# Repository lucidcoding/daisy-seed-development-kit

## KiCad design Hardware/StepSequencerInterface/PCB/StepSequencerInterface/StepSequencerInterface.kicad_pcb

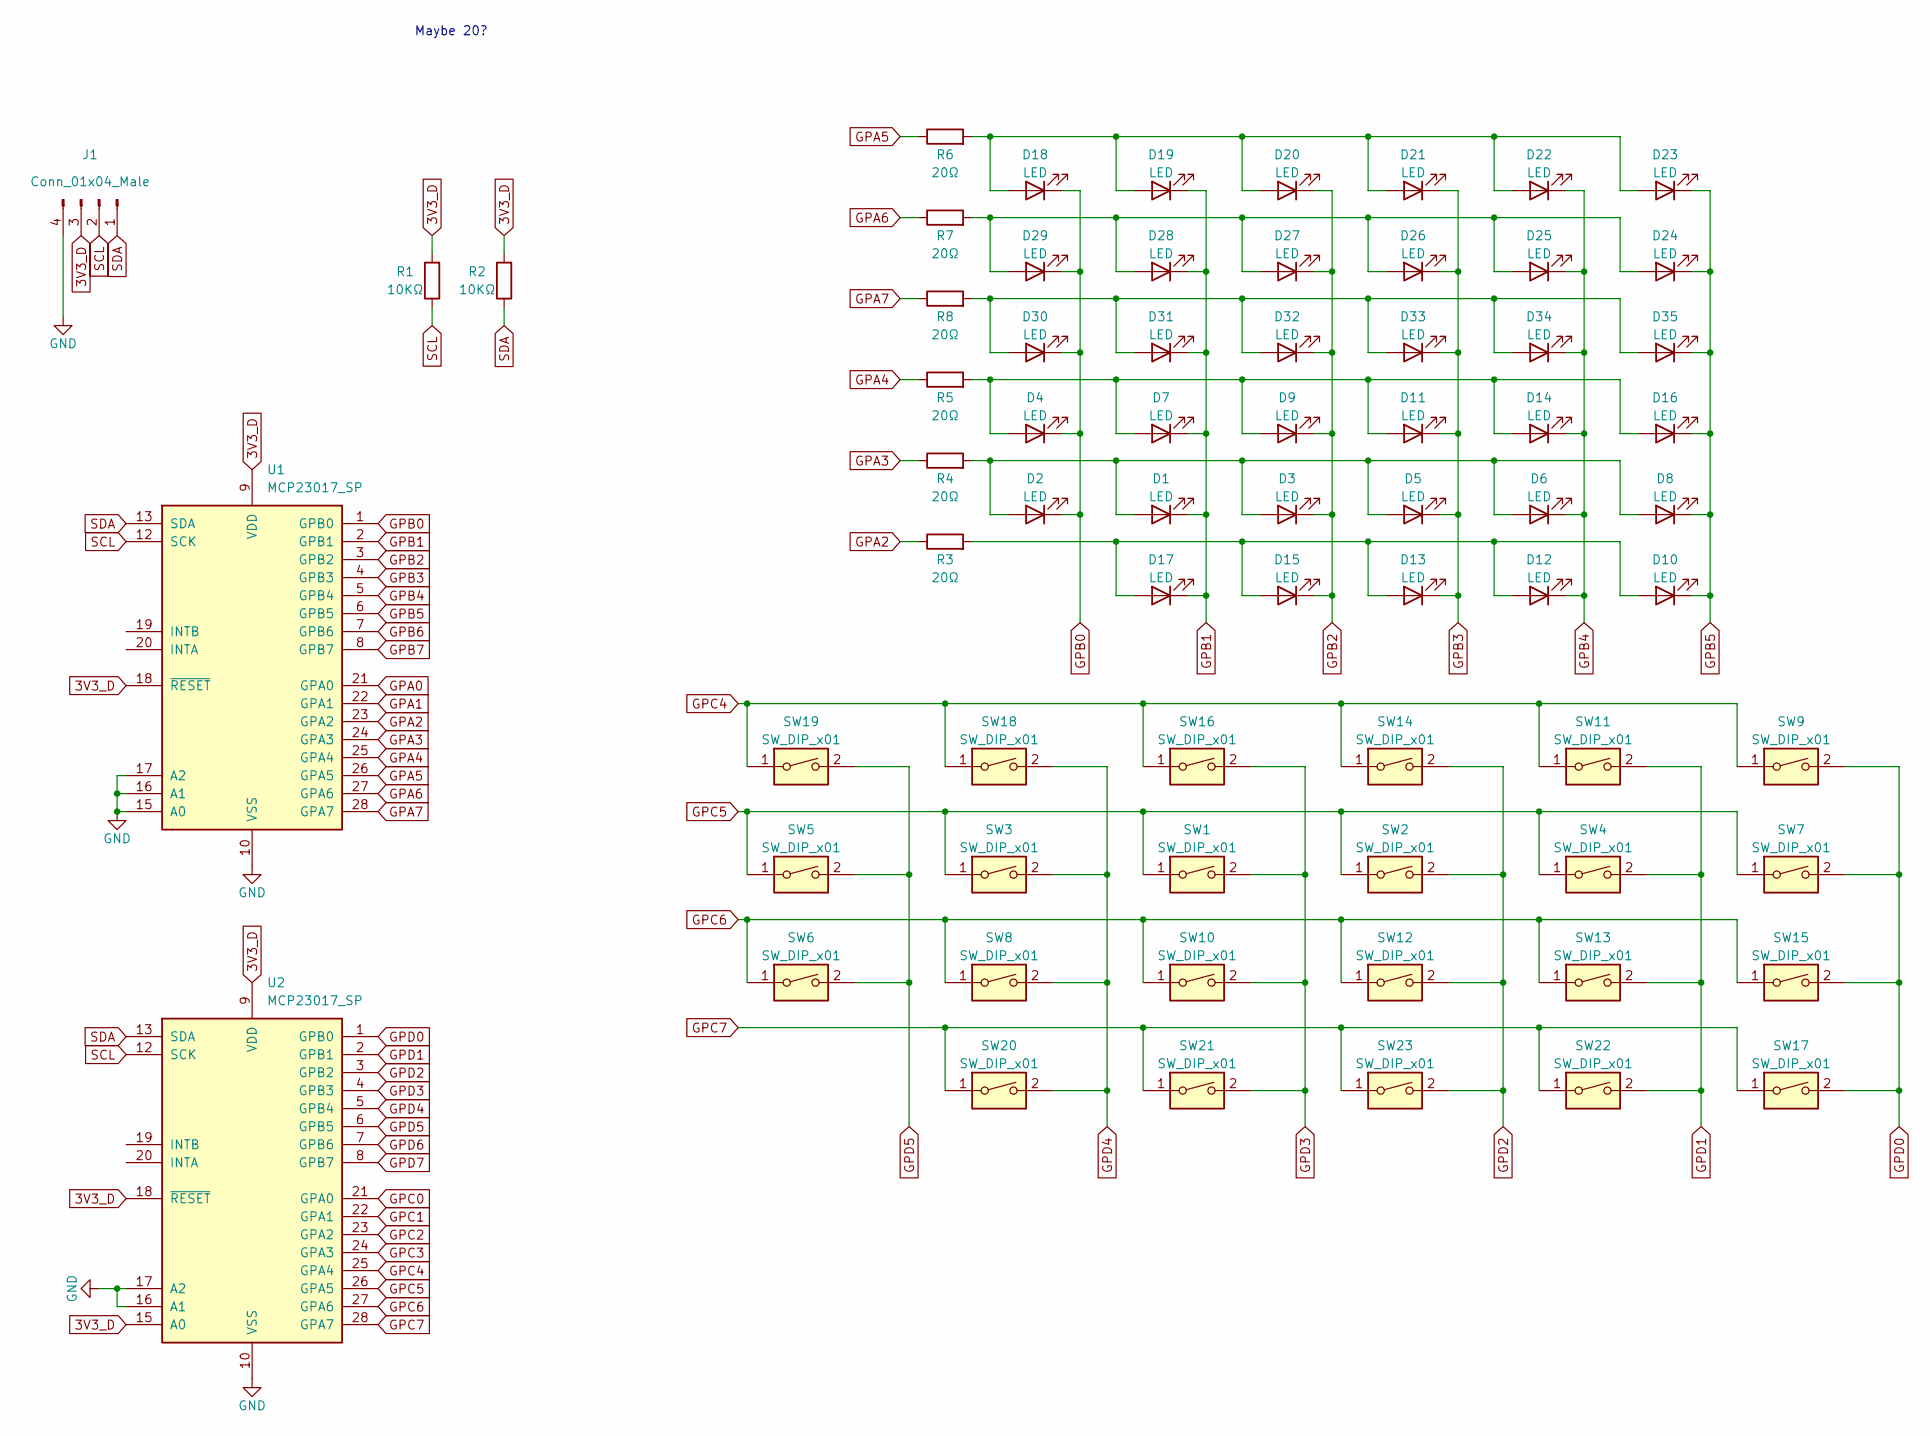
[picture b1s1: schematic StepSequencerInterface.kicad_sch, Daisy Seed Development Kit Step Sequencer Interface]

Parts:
D1, D2, D3, D4, D5, D6, D7, D8, D9, D10, D11, D12, D13, D14, D15, D16, D17, D18, D19, D20, D21, D22, D23, D24, D25, D26, D27, D28, D29, D30, D31, D32, D33, D34, D35: LED; LED_D3.0mm
J1: Conn_01x04_Male; PinSocket_1x04_P2.54mm_Vertical
R1, R2: 10KΩ; R_Axial_DIN0207_L6.3mm_D2.5mm_P10.16mm_Horizontal
R3, R4, R5, R6, R7, R8: 20Ω; R_Axial_DIN0207_L6.3mm_D2.5mm_P10.16mm_Horizontal
SW1, SW2, SW3, SW4, SW5, SW6, SW7, SW8, SW9, SW10, SW11, SW12, SW13, SW14, SW15, SW16, SW17, SW18, SW19, SW20, SW21, SW22, SW23: SW_DIP_x01; SW_PUSH_6mm
U1, U2: MCP23017_SP; DIP-28_W7.62mm

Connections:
3V3_D: J1.3, R1.2, R2.2, U1.9 (VDD), U1.18 (~RESET), U2.9 (VDD), U2.15 (A0), U2.18 (~RESET)
GND: J1.4, U1.10 (VSS), U1.15 (A0), U1.16 (A1), U1.17 (A2), U2.10 (VSS), U2.16 (A1), U2.17 (A2)
GPA0: U1.21 (GPA0)
GPA1: U1.22 (GPA1)
GPA2: R3.1, U1.23 (GPA2)
GPA3: R4.1, U1.24 (GPA3)
GPA4: R5.1, U1.25 (GPA4)
GPA5: R6.1, U1.26 (GPA5)
GPA6: R7.1, U1.27 (GPA6)
GPA7: R8.1, U1.28 (GPA7)
GPB0: D2.1 (K), D4.1 (K), D18.1 (K), D29.1 (K), D30.1 (K), U1.1 (GPB0)
GPB1: D1.1 (K), D7.1 (K), D17.1 (K), D19.1 (K), D28.1 (K), D31.1 (K), U1.2 (GPB1)
GPB2: D3.1 (K), D9.1 (K), D15.1 (K), D20.1 (K), D27.1 (K), D32.1 (K), U1.3 (GPB2)
GPB3: D5.1 (K), D11.1 (K), D13.1 (K), D21.1 (K), D26.1 (K), D33.1 (K), U1.4 (GPB3)
GPB4: D6.1 (K), D12.1 (K), D14.1 (K), D22.1 (K), D25.1 (K), D34.1 (K), U1.5 (GPB4)
GPB5: D8.1 (K), D10.1 (K), D16.1 (K), D23.1 (K), D24.1 (K), D35.1 (K), U1.6 (GPB5)
GPB6: U1.7 (GPB6)
GPB7: U1.8 (GPB7)
GPC0: U2.21 (GPA0)
GPC1: U2.22 (GPA1)
GPC2: U2.23 (GPA2)
GPC3: U2.24 (GPA3)
GPC4: SW9.1, SW11.1, SW14.1, SW16.1, SW18.1, SW19.1, U2.25 (GPA4)
GPC5: SW1.1, SW2.1, SW3.1, SW4.1, SW5.1, SW7.1, U2.26 (GPA5)
GPC6: SW6.1, SW8.1, SW10.1, SW12.1, SW13.1, SW15.1, U2.27 (GPA6)
GPC7: SW17.1, SW20.1, SW21.1, SW22.1, SW23.1, U2.28 (GPA7)
GPD0: SW7.2, SW9.2, SW15.2, SW17.2, U2.1 (GPB0)
GPD1: SW4.2, SW11.2, SW13.2, SW22.2, U2.2 (GPB1)
GPD2: SW2.2, SW12.2, SW14.2, SW23.2, U2.3 (GPB2)
GPD3: SW1.2, SW10.2, SW16.2, SW21.2, U2.4 (GPB3)
GPD4: SW3.2, SW8.2, SW18.2, SW20.2, U2.5 (GPB4)
GPD5: SW5.2, SW6.2, SW19.2, U2.6 (GPB5)
GPD6: U2.7 (GPB6)
GPD7: U2.8 (GPB7)
unnamed: D1.2 (A), D2.2 (A), D3.2 (A), D5.2 (A), D6.2 (A), D8.2 (A), R4.2
unnamed: D4.2 (A), D7.2 (A), D9.2 (A), D11.2 (A), D14.2 (A), D16.2 (A), R5.2
unnamed: D10.2 (A), D12.2 (A), D13.2 (A), D15.2 (A), D17.2 (A), R3.2
unnamed: D18.2 (A), D19.2 (A), D20.2 (A), D21.2 (A), D22.2 (A), D23.2 (A), R6.2
unnamed: D24.2 (A), D25.2 (A), D26.2 (A), D27.2 (A), D28.2 (A), D29.2 (A), R7.2
unnamed: D30.2 (A), D31.2 (A), D32.2 (A), D33.2 (A), D34.2 (A), D35.2 (A), R8.2
SCL: J1.2, R1.1, U1.12 (SCK), U2.12 (SCK)
SDA: J1.1, R2.1, U1.13 (SDA), U2.13 (SDA)

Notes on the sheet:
Maybe 20?

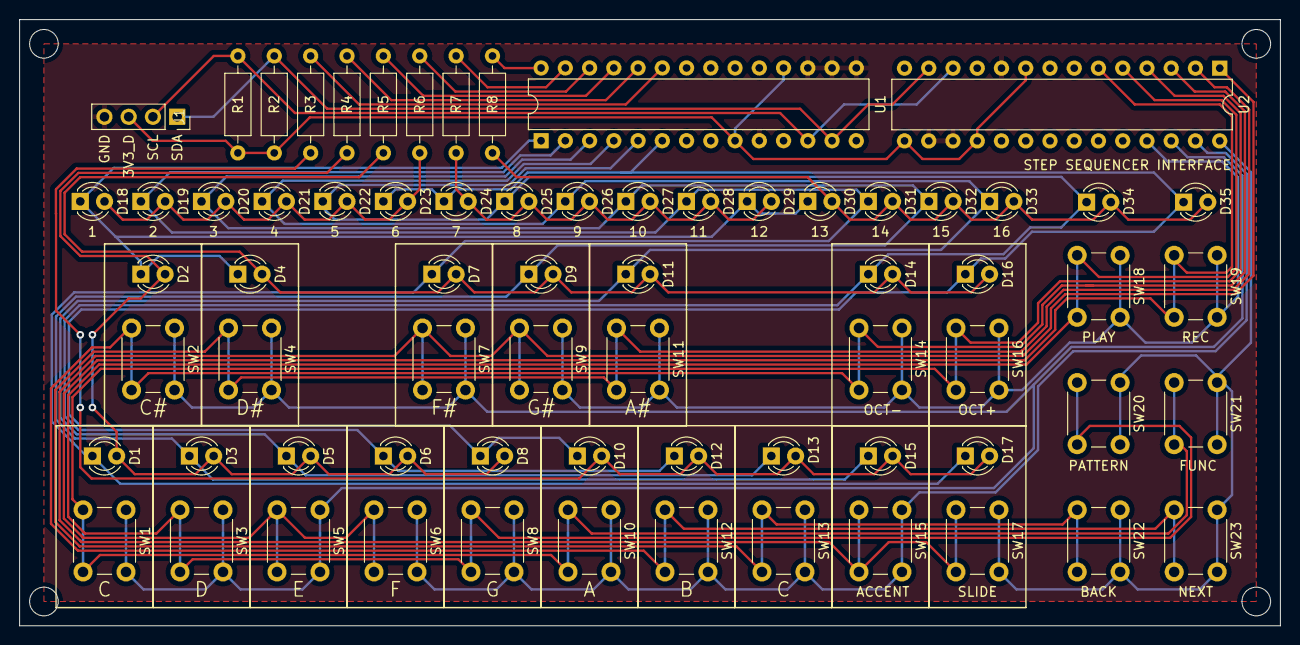
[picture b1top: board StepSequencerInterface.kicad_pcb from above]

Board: 2 copper layers, 132.1 x 63.5 mm, 69 parts (0 on the bottom side), 32 nets.
